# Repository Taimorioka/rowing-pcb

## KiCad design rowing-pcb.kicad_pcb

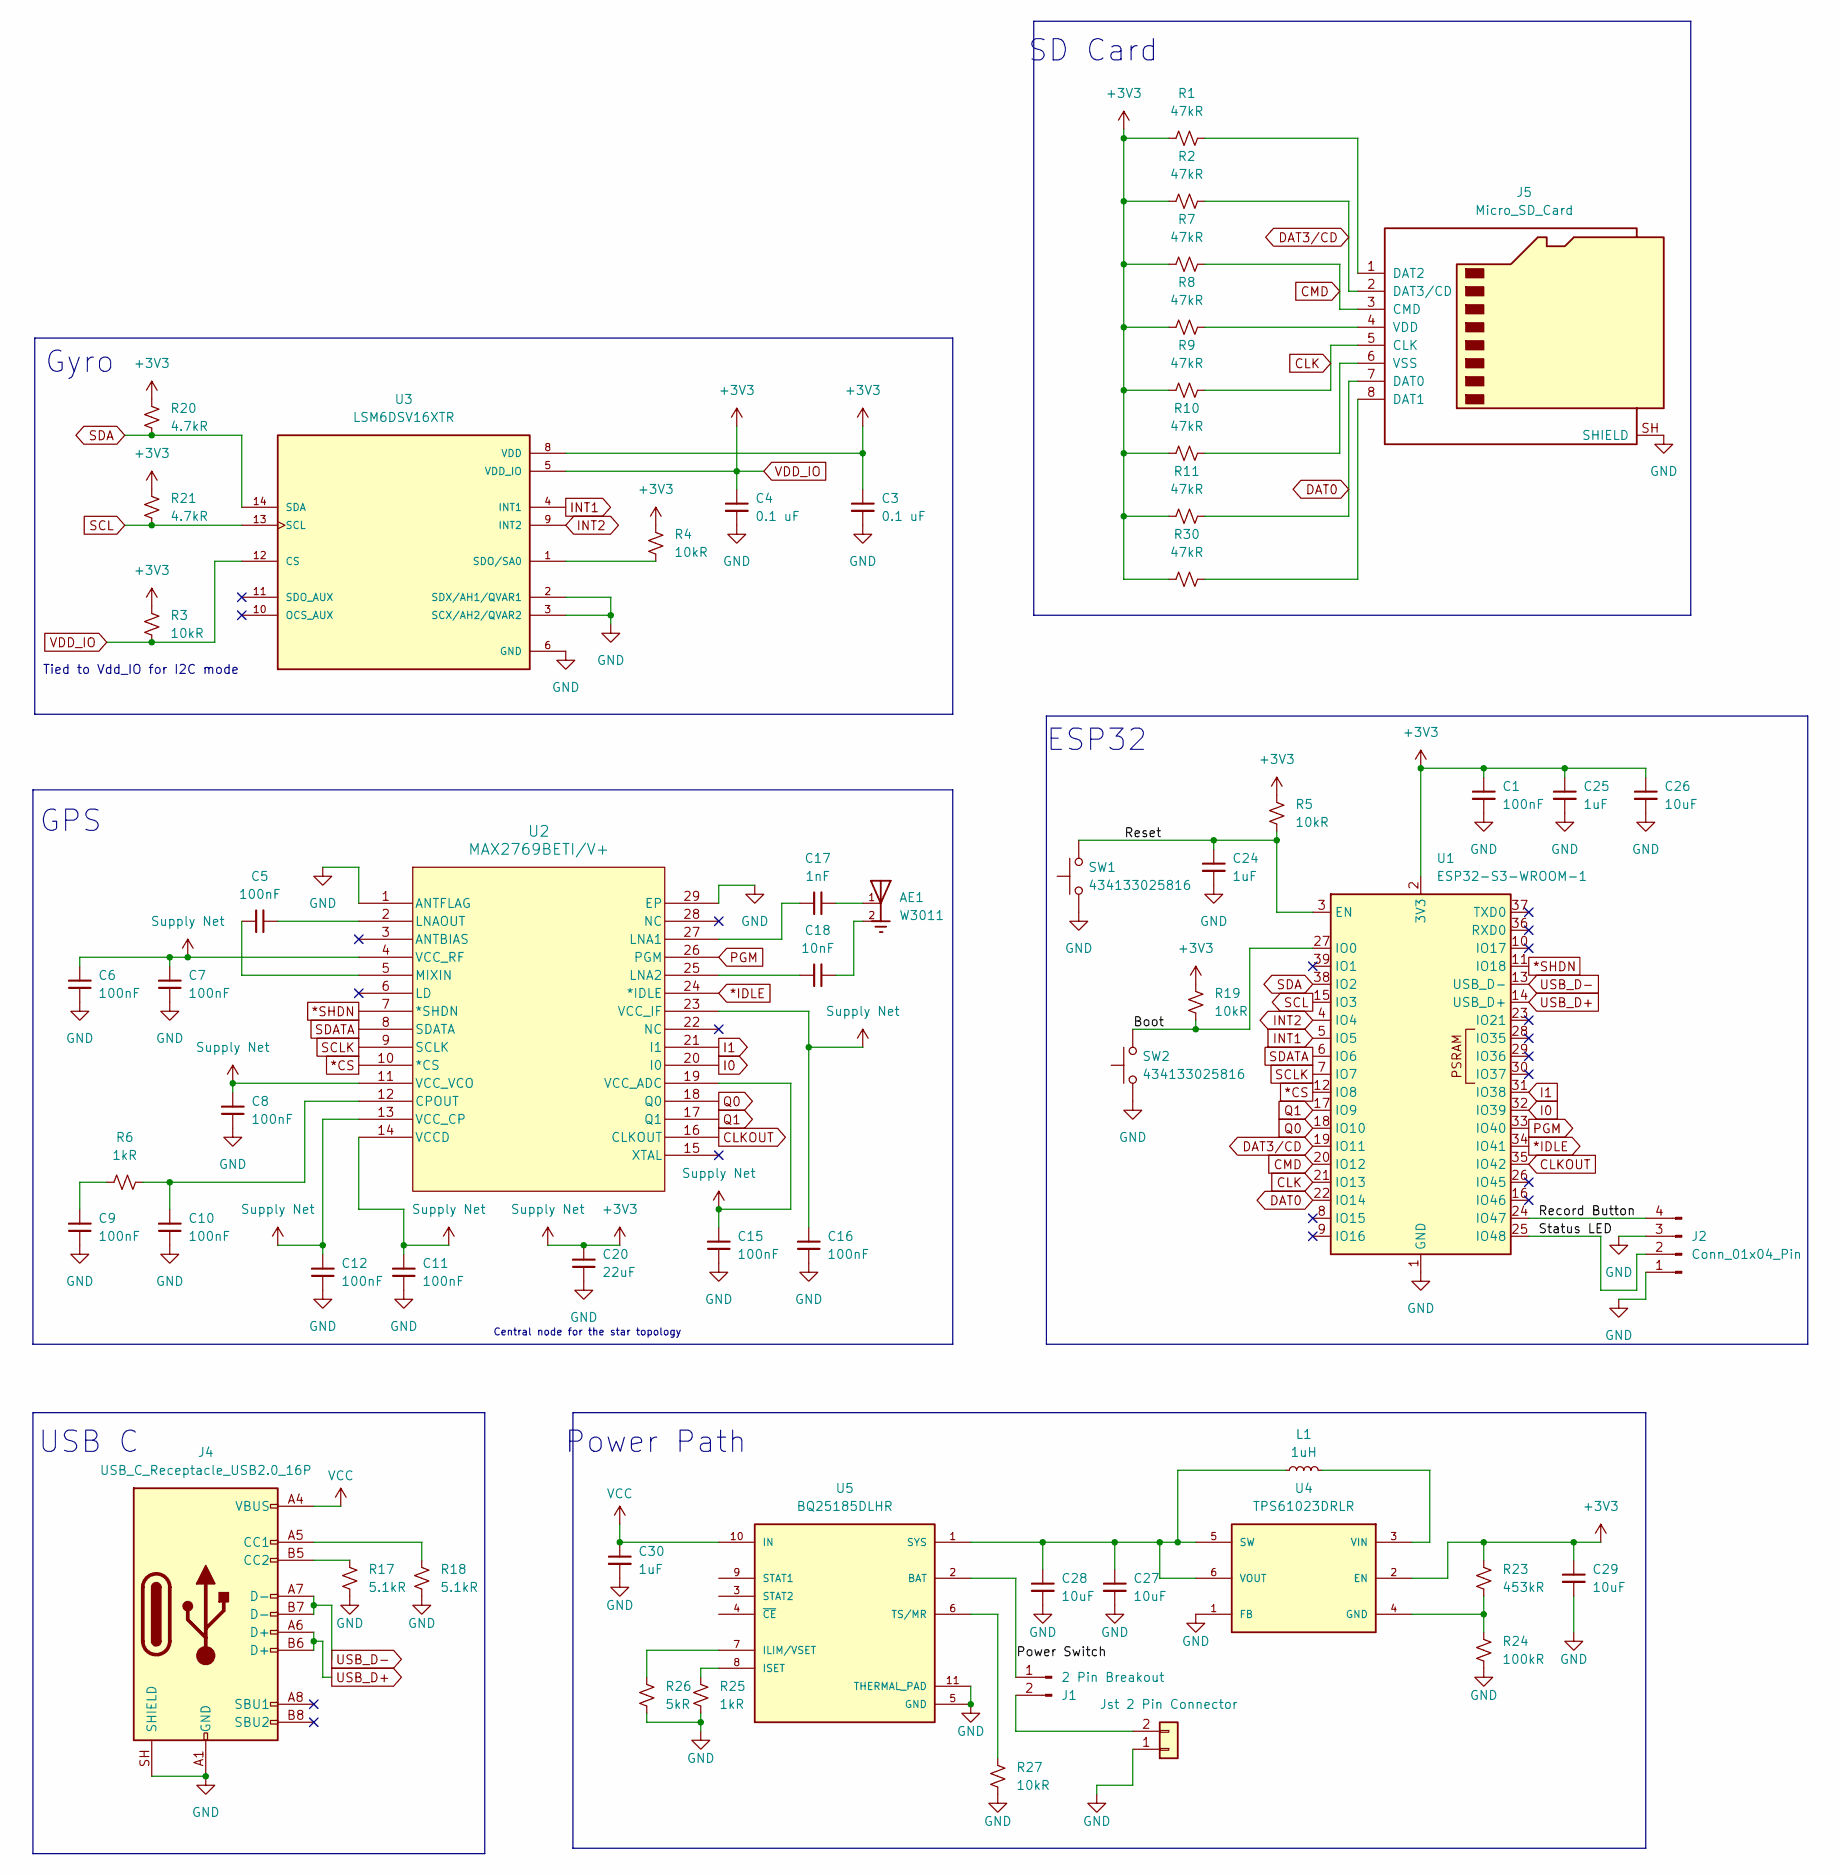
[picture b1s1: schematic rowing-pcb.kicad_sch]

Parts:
AE1: W3011; Pulse_W3011; MPN W3011
C1, C5, C6, C7, C8, C9, C10, C11, C12, C15, C16: 100nF; C_0201_0603Metric_Pad0.64x0.40mm_HandSolder
C3, C4: 0.1 uF; C_0201_0603Metric_Pad0.64x0.40mm_HandSolder
C17: 1nF; C_0201_0603Metric_Pad0.64x0.40mm_HandSolder
C18: 10nF; C_0201_0603Metric_Pad0.64x0.40mm_HandSolder
C20: 22uF; C_0805_2012Metric_Pad1.18x1.45mm_HandSolder
C24, C25, C30: 1uF; C_0201_0603Metric_Pad0.64x0.40mm_HandSolder
C26, C27, C28, C29: 10uF; C_0201_0603Metric_Pad0.64x0.40mm_HandSolder
J1: 2 Pin Breakout; PinHeader_1x02_P1.00mm_Vertical
J2: Conn_01x04_Pin; PinHeader_1x04_P1.00mm_Vertical
J3: Jst 2 Pin Connector; JST_PH_S2B-PH-K_1x02_P2.00mm_Horizontal
J4: USB_C_Receptacle_USB2.0_16P; USB_C_Receptacle_GCT_USB4105-xx-A_16P_TopMnt_Horizontal
J5: Micro_SD_Card; microSD_HC_Wuerth_693072010801
L1: 1uH; L_Abracon_ASPI-0425
R1, R2, R7, R8, R9, R10, R11, R30: 47kR; R_0201_0603Metric_Pad0.64x0.40mm_HandSolder
R3, R4, R5, R19, R27: 10kR; R_0201_0603Metric_Pad0.64x0.40mm_HandSolder
R6, R25: 1kR; R_0201_0603Metric_Pad0.64x0.40mm_HandSolder
R17, R18: 5.1kR; R_0201_0603Metric_Pad0.64x0.40mm_HandSolder
R20, R21: 4.7kR; R_0201_0603Metric_Pad0.64x0.40mm_HandSolder
R23: 453kR; R_0201_0603Metric_Pad0.64x0.40mm_HandSolder
R24: 100kR; R_0201_0603Metric_Pad0.64x0.40mm_HandSolder
R26: 5kR; R_0201_0603Metric_Pad0.64x0.40mm_HandSolder
SW1, SW2: 434133025816; SW_Push_1P1T_NO_Vertical_Wuerth_434133025816
U1: ESP32-S3-WROOM-1
U2: MAX2769BETI/V+; TQFN-28-1EP_5x5mm_P0.5mm_EP3.25x3.25mm_ThermalVias
U3: LSM6DSV16XTR; LGA-14_3x2.5mm_P0.5mm_LayoutBorder3x4y; PARTREV 4
U4: TPS61023DRLR; SOT563-ORI; MPN TPS61023DRLR
U5: BQ25185DLHR; IC_BQ25185DLHR; MPN BQ25185DLHR

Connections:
*CS: U1.12 (IO8), U2.10 (*CS)
*IDLE: U1.34 (IO41), U2.24 (*IDLE)
*SHDN: U1.11 (IO18), U2.7 (*SHDN)
/Boot: R19.2, SW2.2, U1.27 (IO0)
/Power Switch: J1.1, U5.2 (BAT)
/Record Button: J2.4, U1.24 (IO47)
/Reset: C24.1, R5.1, SW1.2, U1.3 (EN)
/Status LED: J2.2, U1.25 (IO48)
<NO NET>: AE1.2, AE1.3, C18.1
CLK: J5.5 (CLK), R9.2, U1.21 (IO13)
CLKOUT: U1.35 (IO42), U2.16 (CLKOUT)
CMD: J5.3 (CMD), R7.2, U1.20 (IO12)
DAT0: J5.7 (DAT0), R11.2, U1.22 (IO14)
DAT3/CD: J5.2 (DAT3/CD), R2.2, U1.19 (IO11)
GND: C1.2, C3.2, C4.2, C6.2, C7.2, C8.2, C9.2, C10.2, C11.2, C12.2, C15.2, C16.2, C20.1, C24.2, C25.2, C26.2, C27.2, C28.2, C29.2, C30.2, J2.1, J2.3, J3.1, J4.A1 (GND), J4.A12 (GND), J4.B1 (GND), J4.B12 (GND), J4.SH (SHIELD), J5.SH (SHIELD), R17.2, R18.2, R24.2, R25.2, R26.2, R27.2, SW1.1, SW2.1, U1.1 (GND), U1.40 (GND), U1.41 (GND), U2.1 (ANTFLAG), U2.29 (EP), U3.2 (SDX/AH1/QVAR1), U3.3 (SCX/AH2/QVAR2), U3.6 (GND), U3.7 (GND), U4.1 (FB), U5.5 (GND), U5.11 (THERMAL_PAD)
I0: U1.32 (IO39), U2.20 (I0)
I1: U1.31 (IO38), U2.21 (I1)
INT1: U1.5 (IO5), U3.4 (INT1)
INT2: U1.4 (IO4), U3.9 (INT2)
unnamed: AE1.1, C17.1
unnamed: C9.1, R6.1
unnamed: J1.2, J3.2
unnamed: J4.A5 (CC1), R18.1
unnamed: J4.B5 (CC2), R17.1
unnamed: J5.8 (DAT1), R30.2
unnamed: J5.1 (DAT2), R1.2
unnamed: J5.4 (VDD), R8.2
unnamed: J5.6 (VSS), R10.2
unnamed: C10.1, R6.2, U2.12 (CPOUT)
unnamed: C17.2, U2.27 (LNA1)
unnamed: C18.2, U2.25 (LNA2)
unnamed: C5.1, U2.2 (LNAOUT)
unnamed: C5.2, U2.5 (MIXIN)
unnamed: R4.1, U3.1 (SDO/SA0)
unnamed: R23.2, R24.1, U4.4 (GND)
unnamed: C27.1, C28.1, L1.1, U4.5 (SW), U4.6 (VOUT), U5.1 (SYS)
unnamed: L1.2, U4.3 (VIN)
unnamed: R26.1, U5.7 (ILIM/VSET)
unnamed: R25.1, U5.8 (ISET)
unnamed: R27.1, U5.6 (TS/MR)
PGM: U1.33 (IO40), U2.26 (PGM)
Q0: U1.18 (IO10), U2.18 (Q0)
Q1: U1.17 (IO9), U2.17 (Q1)
SCL: R21.2, U1.15 (IO3), U3.13 (SCL)
SCLK: U1.7 (IO7), U2.9 (SCLK)
SDA: R20.1, U1.38 (IO2), U3.14 (SDA)
SDATA: U1.6 (IO6), U2.8 (SDATA)
USB_D+: J4.A6 (D+), J4.B6 (D+), U1.14 (USB_D+)
USB_D-: J4.A7 (D-), J4.B7 (D-), U1.13 (USB_D-)
VCC: C30.1, J4.A4 (VBUS), J4.A9 (VBUS), J4.B4 (VBUS), J4.B9 (VBUS), U5.10 (IN)
VDD_IO: C1.1, C3.1, C4.1, C6.1, C7.1, C8.1, C11.1, C12.1, C15.1, C16.1, C20.2, C25.1, C26.1, C29.1, R1.1, R2.1, R3.1, R3.2, R4.2, R5.2, R7.1, R8.1, R9.1, R10.1, R11.1, R19.1, R20.2, R21.1, R23.1, R30.1, U1.2 (3V3), U2.4 (VCC_RF), U2.11 (VCC_VCO), U2.13 (VCC_CP), U2.14 (VCCD), U2.19 (VCC_ADC), U2.23 (VCC_IF), U3.5 (VDD_IO), U3.8 (VDD), U3.12 (CS), U4.2 (EN)

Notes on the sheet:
Central node for the star topology
Power Path
USB C
SD Card
ESP32
Tied to Vdd_IO for I2C mode
Gyro
GPS

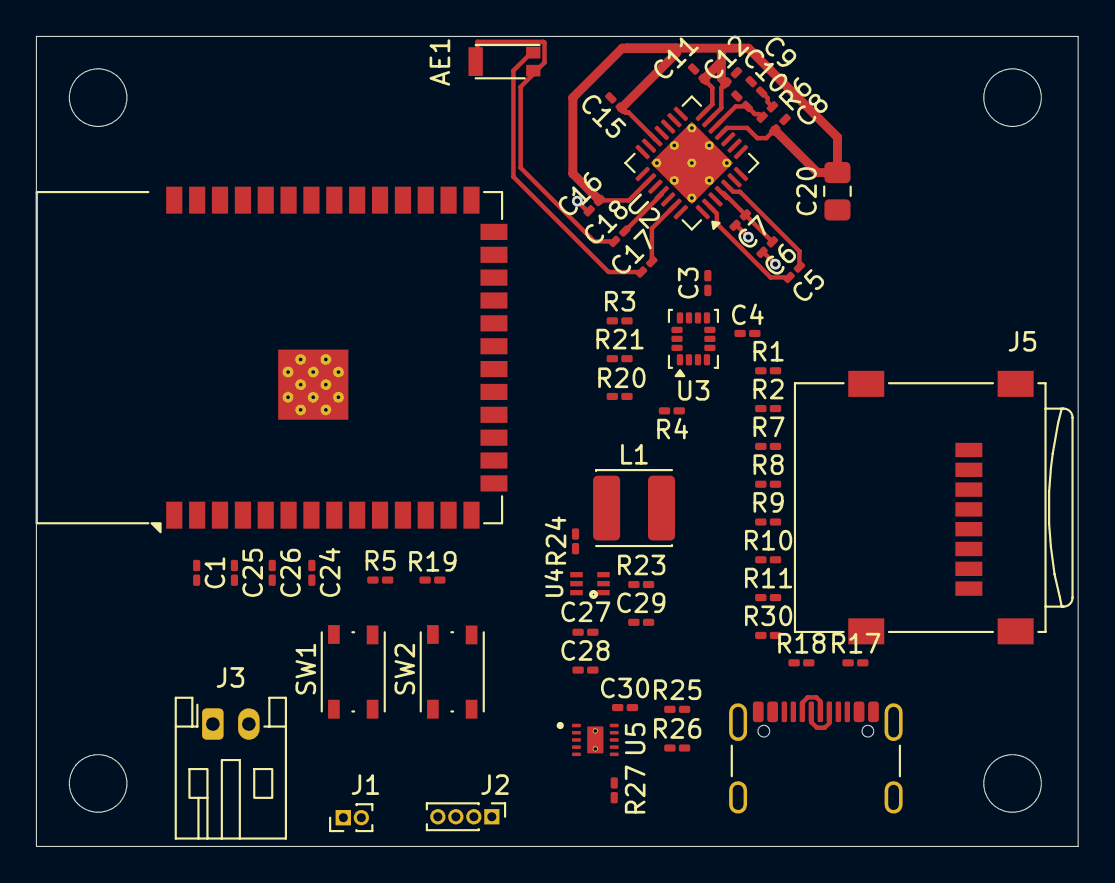
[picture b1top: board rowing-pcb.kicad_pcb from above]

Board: 4 copper layers, 57.9 x 45.0 mm, 59 parts (0 on the bottom side), 51 nets.
